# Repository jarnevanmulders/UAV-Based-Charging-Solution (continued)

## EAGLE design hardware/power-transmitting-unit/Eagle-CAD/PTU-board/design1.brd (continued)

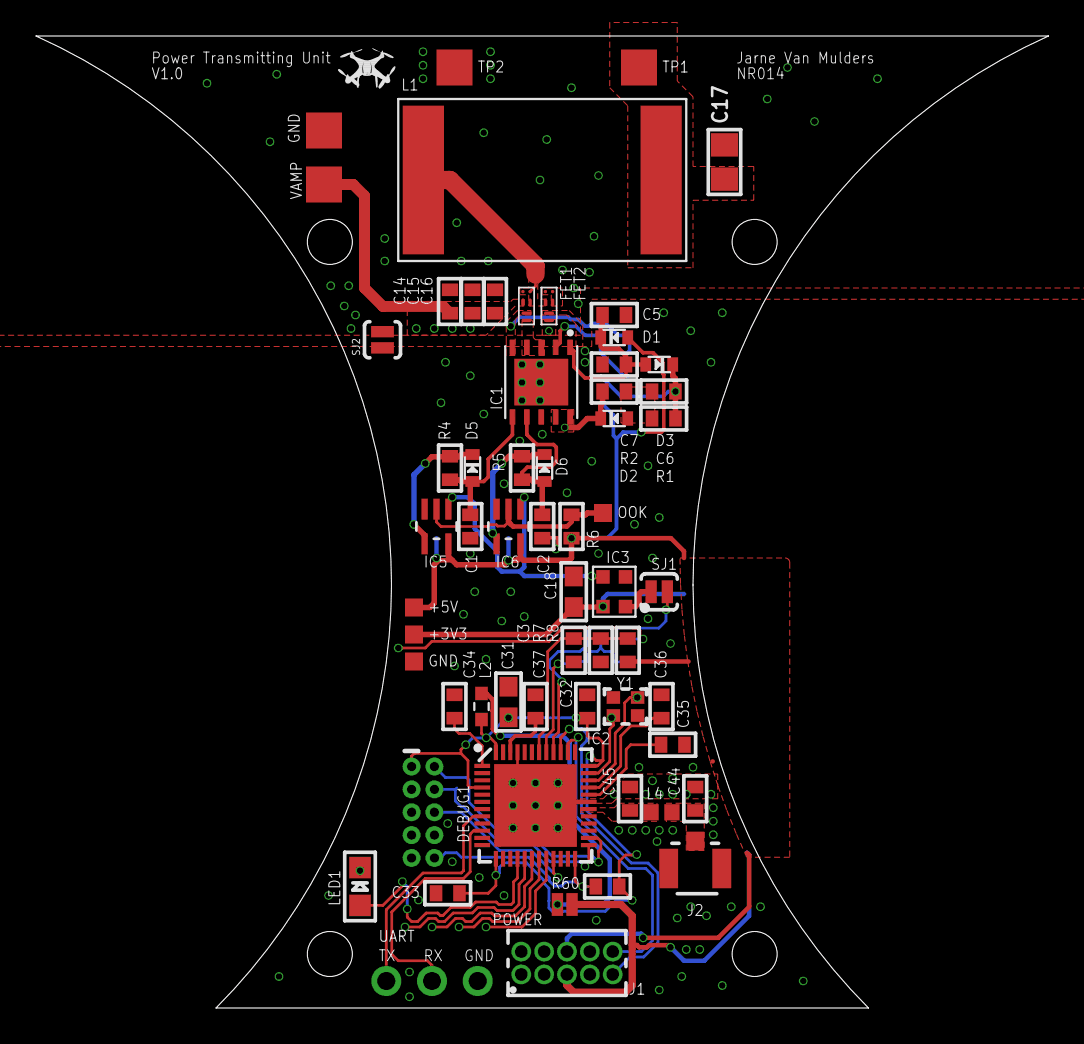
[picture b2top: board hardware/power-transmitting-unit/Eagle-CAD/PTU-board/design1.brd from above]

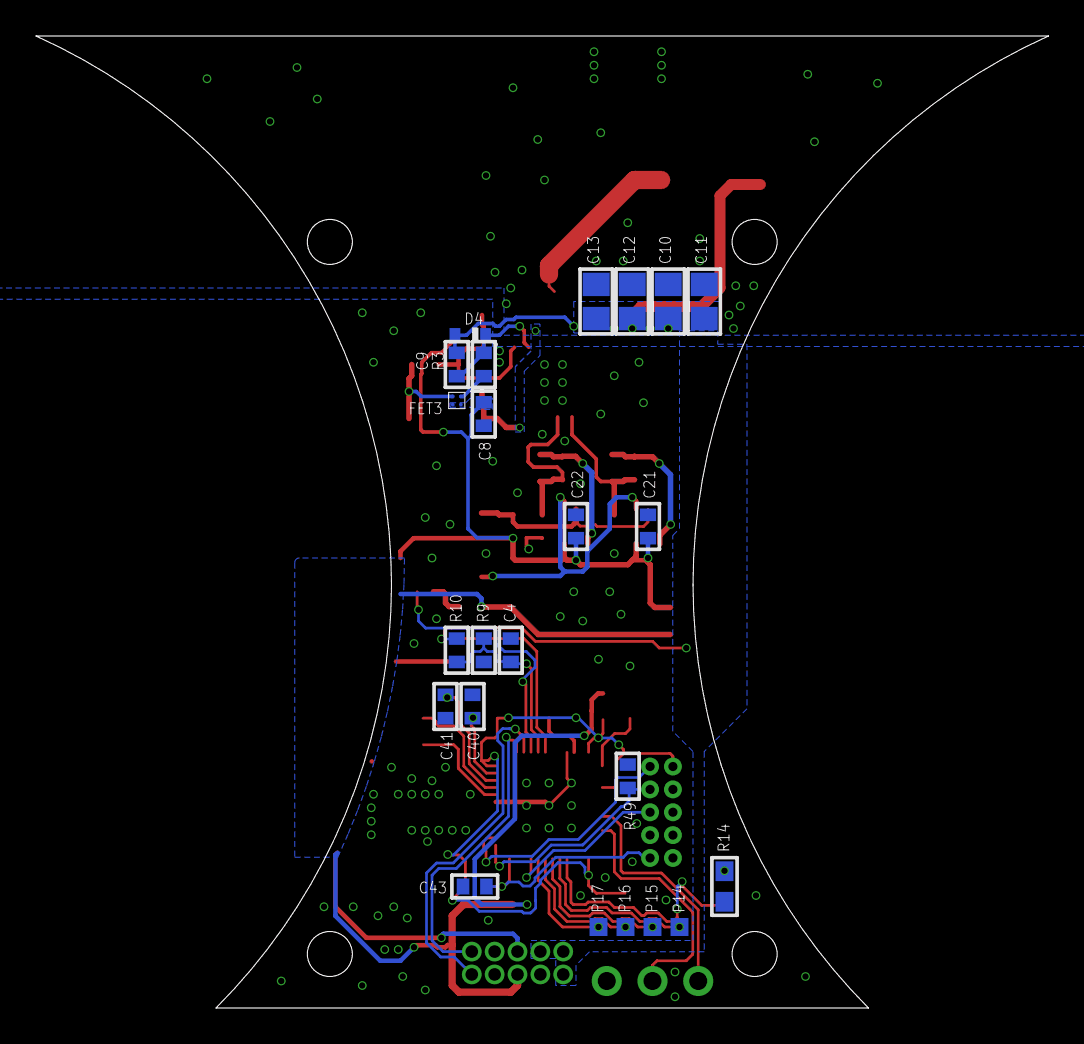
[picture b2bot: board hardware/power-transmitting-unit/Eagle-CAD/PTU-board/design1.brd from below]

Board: 2 copper layers, 56.2 x 54.0 mm, 83 parts (23 on the bottom side), 49 nets.

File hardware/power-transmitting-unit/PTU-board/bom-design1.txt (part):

Partlist exported from C:/Users/jarne/Documents/GitHub/IoT_energystorage_charger_ble/hardware/power-transmitting-unit/PTU-board/design1.sch at 05/09/2023 14:39

Part   Value                   Device                      Package                 Description                                                                                          AVAILABILITY DATASHEET-URL                                                DESCRIPTION                                                                            GENDER         IR MF                MOUNT MP                  PACKAGE                   PACKAGING PART-NUMBER   PINS PITCH  POPULARITY PRICE PROD_ID    PURCHASE-URL                                                     ROWS TP_SIGNAL_NAME TYPE     VALUE         WE-NUMBER                 Z    
C1     22p                     CAP_CERAMIC0402             0402                    Ceramic Capacitors                                                                                                                                                                                                                                                                                                                                                                                                                                                                                                                                                       
C2     22p                     CAP_CERAMIC0402             0402                    Ceramic Capacitors                                                                                                                                                                                                                                                                                                                                                                                                                                                                                                                                                       
C3     100n                    CAP_CERAMIC0402             0402                    Ceramic Capacitors                                                                                                                                                                                                                                                                                                                                                                                                                                                                                                                                                       
C4     100n                    CAP_CERAMIC0402             0402                    Ceramic Capacitors                                                                                                                                                                                                                                                                                                                                                                                                                                                                                                                                                       
C5     1u                      CAP_CERAMIC0402             0402                    Ceramic Capacitors                                                                                                                                                                                                                                                                                                                                                                                                                                                                                                                                                       
C6     22n                     CAP_CERAMIC0402             0402                    Ceramic Capacitors                                                                                                                                                                                                                                                                                                                                                                                                                                                                                                                                                       
C7     22n                     CAP_CERAMIC0402             0402                    Ceramic Capacitors                                                                                                                                                                                                                                                                                                                                                                                                                                                                                                                                                       
C8     1u                      CAP_CERAMIC0402             0402                    Ceramic Capacitors                                                                                                                                                                                                                                                                                                                                                                                                                                                                                                                                                       
C9     1u                      CAP_CERAMIC0402             0402                    Ceramic Capacitors                                                                                                                                                                                                                                                                                                                                                                                                                                                                                                                                                       
C10    1u                      CAP_CERAMIC0805             0805                    Ceramic Capacitors                                                                                                                                                                                                                                                                                                                                                                                                                                                                                                                                                       
C11    1u                      CAP_CERAMIC0805             0805                    Ceramic Capacitors                                                                                                                                                                                                                                                                                                                                                                                                                                                                                                                                                       
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
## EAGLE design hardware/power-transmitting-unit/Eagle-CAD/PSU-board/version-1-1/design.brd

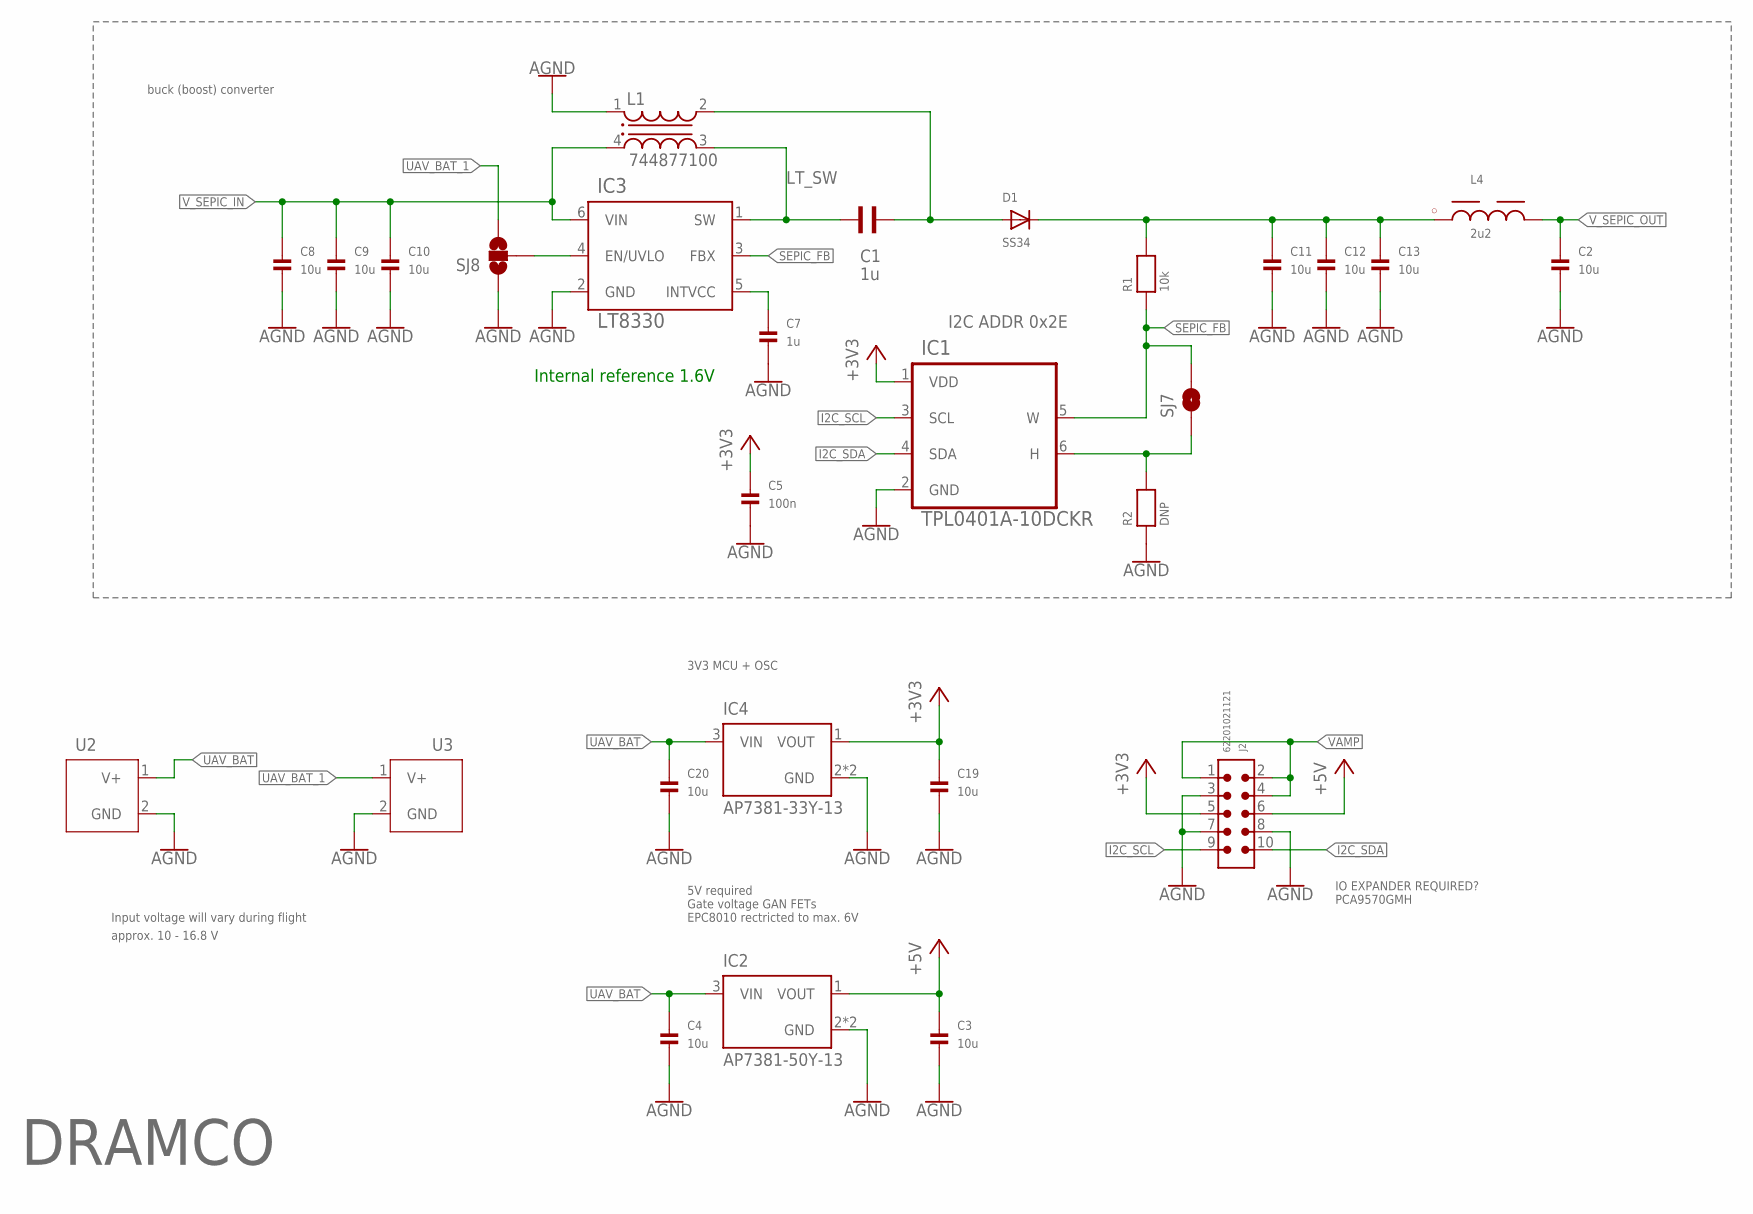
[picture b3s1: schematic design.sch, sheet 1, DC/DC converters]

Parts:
C1: 1u; WCAP-CSGP_0805_WAVE
C2: 10u; 0805
C3, C4, C19, C20: 10u; 0603
C5: 100n; 0402
C7: 1u; 0603
C8, C9, C10, C11, C12, C13: 10u; 1206
D1: SS34; SOD-123
IC1: TPL0401A-10DCKR; SOT65P210X110-6N
IC2: AP7381-50Y-13; FOOT_XC6201P332PR-G
IC3: LT8330; TSOT-23_S6
IC4: AP7381-33Y-13; FOOT_XC6201P332PR-G
J2: 62201021121
L1: 744877100; WE-DD_7345
L4: 2u2; WE-LQS_3015
R1: 10k; 0603
R2: DNP; 0603
SJ7: SOLDERJUMPERNO; SJ_2S-NO
SJ8: SOLDERJUMPER_2WAYS; SJ_3
U2, U3: UAV-CONNECT; HOLE

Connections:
+3V3: C5.1, C19.1, IC1.1 (VDD), IC4.1 (VOUT), J2.5; also elsewhere on the board
+5V: C3.1, IC2.1 (VOUT), J2.6; also elsewhere on the board
AGND: C2.2, C3.2, C4.2, C5.2, C7.2, C8.2, C9.2, C10.2, C11.2, C12.2, C13.2, C19.2, C20.2, IC1.2 (GND), IC2.2 (GND), IC2.2.1 (GND), IC3.2 (GND), IC4.2 (GND), IC4.2.1 (GND), J2.3, J2.7, J2.8, L1.1, R2.1, SJ8.1, U2.2 (GND), U3.2 (GND); also elsewhere on the board
I2C_SCL: IC1.3 (SCL), J2.9; also elsewhere on the board
I2C_SDA: IC1.4 (SDA), J2.10; also elsewhere on the board
LT_SW: C1.2, IC3.1 (SW), L1.3
unnamed: C7.1, IC3.5 (INTVCC)
unnamed: C1.1, D1.A, L1.2
unnamed: C11.1, C12.1, C13.1, D1.C, L4.1, R1.2
unnamed: IC3.4 (EN/UVLO), SJ8.2
unnamed: IC1.6 (H), R2.2, SJ7.1
SEPIC_FB: IC1.5 (W), IC3.3 (FBX), R1.1, SJ7.2
UAV_BAT: C4.1, C20.1, IC2.3 (VIN), IC4.3 (VIN), U2.1 (V+); also elsewhere on the board
UAV_BAT_1: SJ8.3, U3.1 (V+); also elsewhere on the board
VAMP: J2.1, J2.2, J2.4; also elsewhere on the board
V_SEPIC_IN: C8.1, C9.1, C10.1, IC3.6 (VIN), L1.4; also elsewhere on the board
V_SEPIC_OUT: C2.1, L4.2; also elsewhere on the board

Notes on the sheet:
5V required Gate voltage GAN FETs EPC8010 rectricted to max. 6V
buck (boost) converter
Input voltage will vary during flight
approx. 10 - 16.8 V
3V3 MCU + OSC
IO EXPANDER REQUIRED? PCA9570GMH
DRAMCO
I2C ADDR 0x2E
Internal reference 1.6V

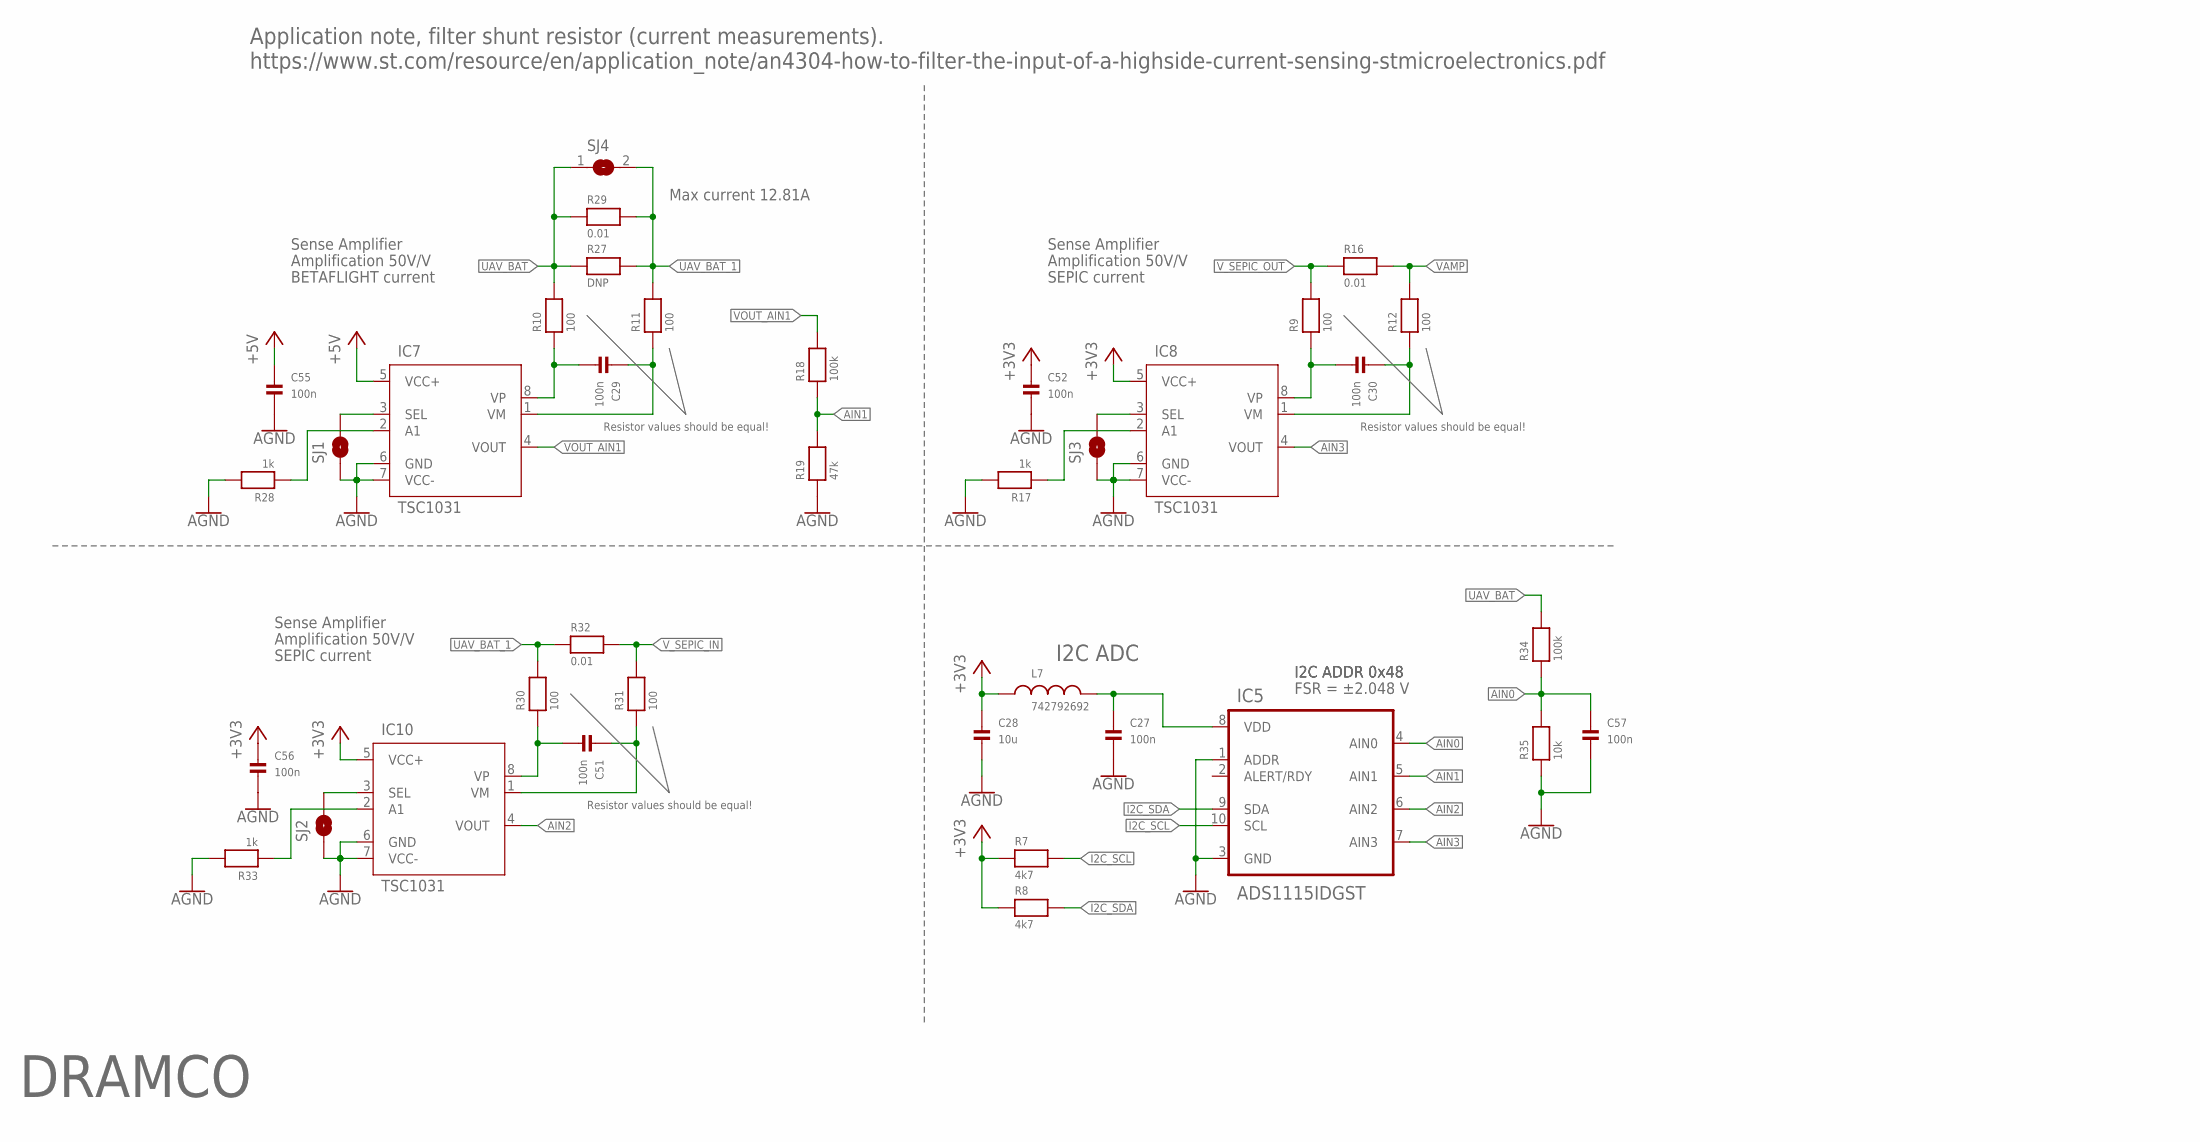
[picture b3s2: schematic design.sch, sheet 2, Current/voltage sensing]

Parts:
C27, C29, C30, C51, C52, C55, C56, C57: 100n; 0402
C28: 10u; 0603
IC5: ADS1115IDGST; SOP50P490X110-10N
IC7, IC8, IC10: TSC1031; SOP65P640X120-8N
L7: 742792692; WE-CBF_0603(W=2.2)
R7, R8: 4k7; 0603
R9, R10, R11, R12, R30, R31: 100; 0402
R16, R29, R32: 0.01; 0805
R17, R28, R33: 1k; 0402
R18, R34: 100k; 0603
R19: 47k; 0603
R27: DNP; 0805
R35: 10k; 0603
SJ1, SJ2, SJ3: SOLDERJUMPERTRACE; SJ_2S-TRACE
SJ4: SOLDERJUMPERREFLOW; SOLDERJUMPER_REFLOW

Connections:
+3V3: C28.1, C52.1, C56.1, IC8.5 (VCC+), IC10.5 (VCC+), L7.1, R7.1, R8.1; also elsewhere on the board
+5V: C55.1, IC7.5 (VCC+); also elsewhere on the board
AGND: C27.2, C28.2, C52.2, C55.2, C56.2, C57.2, IC5.1 (ADDR), IC5.3 (GND), IC7.6 (GND), IC7.7 (VCC-), IC8.6 (GND), IC8.7 (VCC-), IC10.6 (GND), IC10.7 (VCC-), R17.2, R19.1, R28.2, R33.2, R35.1, SJ1.1, SJ2.1, SJ3.1; also elsewhere on the board
AIN0: C57.1, IC5.4 (AIN0), R34.1, R35.2
AIN1: IC5.5 (AIN1), R18.1, R19.2
AIN2: IC5.6 (AIN2), IC10.4 (VOUT)
AIN3: IC5.7 (AIN3), IC8.4 (VOUT)
I2C_SCL: IC5.10 (SCL), R7.2; also elsewhere on the board
I2C_SDA: IC5.9 (SDA), R8.2; also elsewhere on the board
unnamed: C30.1, IC8.1 (VM), R12.1
unnamed: C27.1, IC5.8 (VDD), L7.2
unnamed: C30.2, IC8.8 (VP), R9.1
unnamed: IC8.3 (SEL), SJ3.2
unnamed: IC8.2 (A1), R17.1
unnamed: IC7.3 (SEL), SJ1.2
unnamed: C29.1, IC7.1 (VM), R11.1
unnamed: C29.2, IC7.8 (VP), R10.1
unnamed: C51.1, IC10.1 (VM), R31.1
unnamed: C51.2, IC10.8 (VP), R30.1
unnamed: IC7.2 (A1), R28.1
unnamed: IC10.3 (SEL), SJ2.2
unnamed: IC10.2 (A1), R33.1
UAV_BAT: R10.2, R27.1, R29.1, R34.2, SJ4.1; also elsewhere on the board
UAV_BAT_1: R11.2, R27.2, R29.2, R30.2, R32.1, SJ4.2; also elsewhere on the board
VAMP: R12.2, R16.2; also elsewhere on the board
VOUT_AIN1: IC7.4 (VOUT), R18.2
V_SEPIC_IN: R31.2, R32.2; also elsewhere on the board
V_SEPIC_OUT: R9.2, R16.1; also elsewhere on the board

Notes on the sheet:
I2C ADC
Application note, filter shunt resistor (current measurements). https://www.st.com/resource/en/application_note/an4304-how-to-filter-the-input-of-a-highside-current-sensing-stmicroelectronics.pdf
Sense Amplifier
FSR = ±2.048 V
Resistor values should be equal!
Amplification 50V/V
BETAFLIGHT current
SEPIC current
DRAMCO
I2C ADDR 0x48
Max current 12.81A

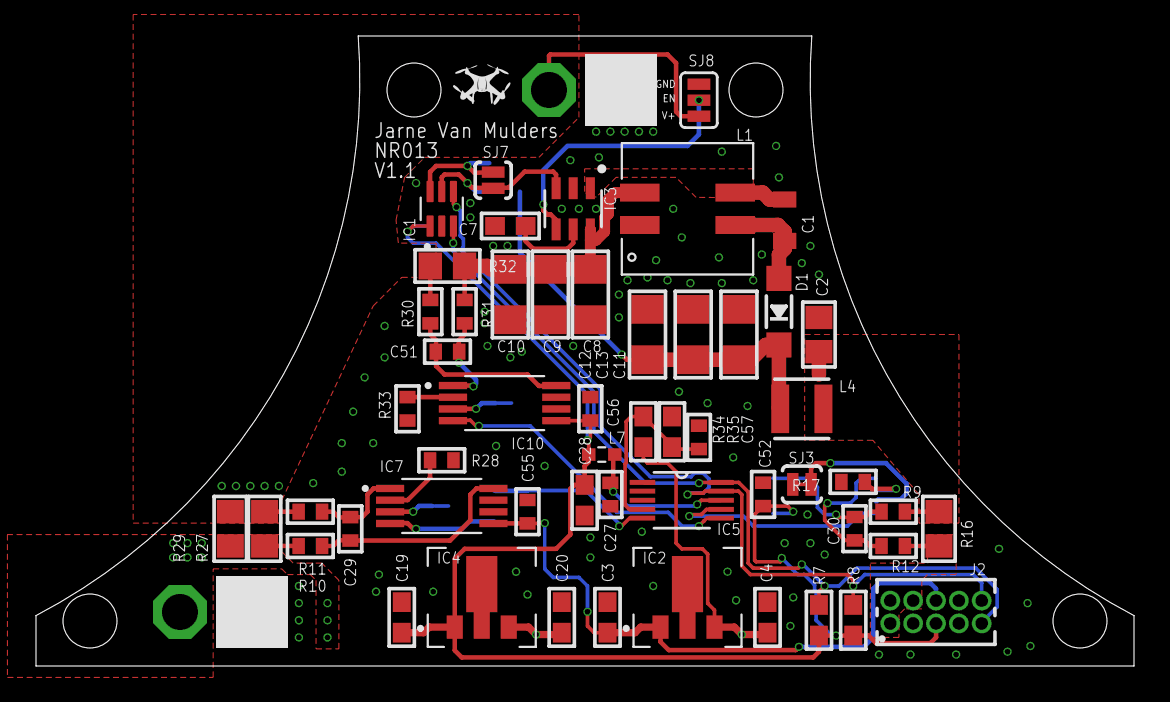
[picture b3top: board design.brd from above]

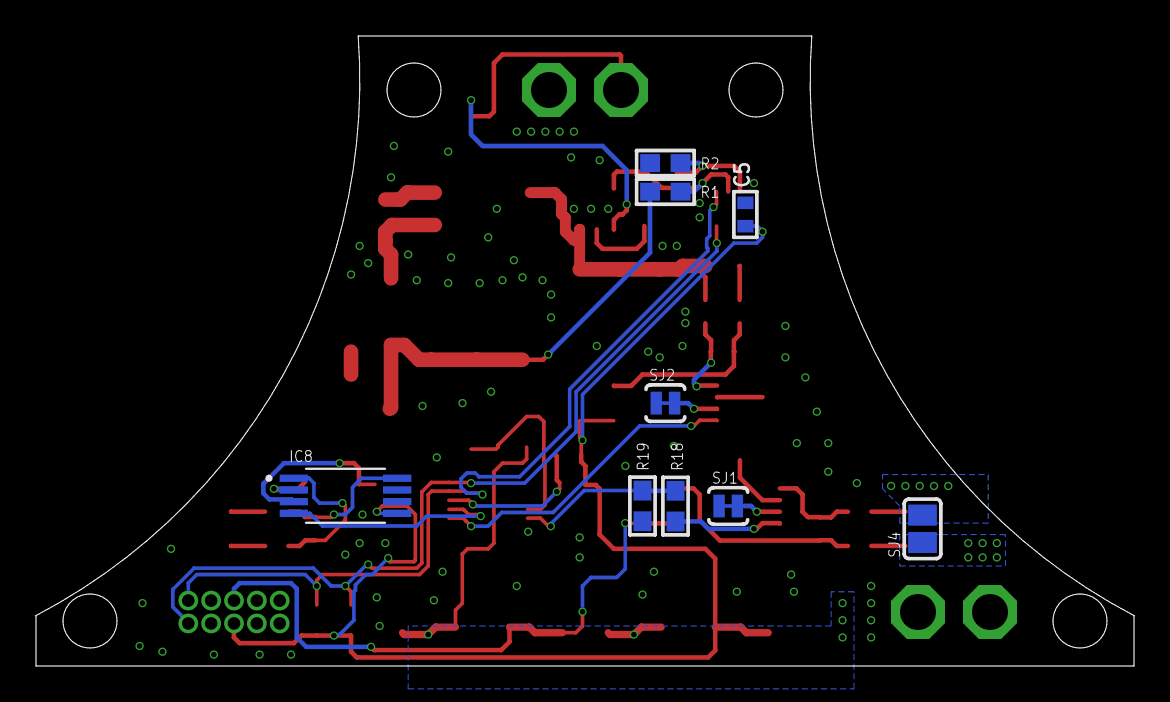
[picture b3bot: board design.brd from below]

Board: 2 copper layers, 61.0 x 35.0 mm, 65 parts (9 on the bottom side), 35 nets.

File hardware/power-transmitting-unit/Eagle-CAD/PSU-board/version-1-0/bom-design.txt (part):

Partlist exported from C:/Users/jarne/Documents/GitHub/IoT_energystorage_charger_ble/hardware/power-transmitting-unit/PSU-board/design.sch at 05/09/2023 14:34

Part Value             Device                           Package             Description                                                   AVAILABILITY CHECK_PRICES                                                                       DATASHEET-URL                                           DESCRIPTION                                                                                                                               GENDER     IR MF                MOUNT MP                PACKAGE                      PACKAGING PART-NUMBER   PINS PITCH  PRICE PURCHASE-URL                                                 ROWS SNAPEDA_LINK                                                                        TYPE     VALUE         WE-NUMBER                
C1   1u                WCAP-CSGP_0805_885012207103_WAVE WCAP-CSGP_0805_WAVE WCAP-CSGP Ceramic Capacitors                                                                                                                                                                                                                                                                                                                                                                                                                                                                                                                                                                                                                                                                         
C2   10u               CAP_CERAMIC0805                  0805                Ceramic Capacitors                                                                                                                                                                                                                                                                                                                                                                                                                                                                                                                                                                                                                                                                                   
C3   10u               CAP_CERAMIC0603                  0603                Ceramic Capacitors                                                                                                                                                                                                                                                                                                                                                                                                                                                                                                                                                                                                                                                                                   
C4   10u               CAP_CERAMIC0603                  0603                Ceramic Capacitors                                                                                                                                                                                                                                                                                                                                                                                                                                                                                                                                                                                                                                                                                   
C5   100n              CAP_CERAMIC0402                  0402                Ceramic Capacitors                                                                                                                                                                                                                                                                                                                                                                                                                                                                                                                                                                                                                                                                                   
C7   1u                CAP_CERAMIC0603                  0603                Ceramic Capacitors                                                                                                                                                                                                                                                                                                                                                                                                                                                                                                                                                                                                                                                                                   
C8   10u               CAP_CERAMIC1206                  1206                Ceramic Capacitors                                                                                                                                                                                                                                                                                                                                                                                                                                                                                                                                                                                                                                                                                   
C9   10u               CAP_CERAMIC1206                  1206                Ceramic Capacitors                                                                                                                                                                                                                                                                                                                                                                                                                                                                                                                                                                                                                                                                                   
C10  10u               CAP_CERAMIC1206                  1206                Ceramic Capacitors                                                                                                                                                                                                                                                                                                                                                                                                                                                                                                                                                                                                                                                                                   
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
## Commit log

2023-06-28 Init commit tests
2023-06-28 change to ibeacon example
2023-06-29 Add PCB files
2023-06-29 Add observer filter
2023-07-02 kicad files
2023-07-03 update pcb + test ltspice
2023-07-03 Update wpt-receiver adv message lib
2023-07-03 make firmware folder
2023-07-03 adaptations
2023-07-03 update pcb
2023-07-04 draft scheme power-receiving-unit
2023-07-04 trying to get ADC working
2023-07-18 power receiving unit PCB V1.0 ready
2023-07-20 ADC reads successfully added and tested
2023-07-20 adc lib + deep sleep added
2023-08-07 Continued to work on design PTU
2023-08-09 ltspice buck-boost
2023-08-09 Update HW PTU
2023-08-16 Update SW PRU & HW PRU + PTU
2023-08-21 Update PRU HW + firmware (send pru info via BLE adv)
2023-09-01 Update hardware PTU
2023-09-01 Add ptu board file
2023-09-01 Update PTU firmware and hardware
2023-09-13 Update PTU firmware
    Add ADS1115 library
2023-09-21 Update firmware PSU (PTU) board (soldering and testing)
2023-09-27 Update firmware and reorganization folders
2023-09-27 Update drawio figure
2023-10-13 Add svg files hardware
2023-10-20 Update firmware - hardware all
2023-10-20 Update PRU board dts file
2023-11-09 Update firmware logger + add python scripts
2023-11-14 update scripts
2023-11-20 Last updates before paper submission
2023-12-20 Measurement setup figure
2023-12-20 Add measurement setup
2023-12-20 update figures
